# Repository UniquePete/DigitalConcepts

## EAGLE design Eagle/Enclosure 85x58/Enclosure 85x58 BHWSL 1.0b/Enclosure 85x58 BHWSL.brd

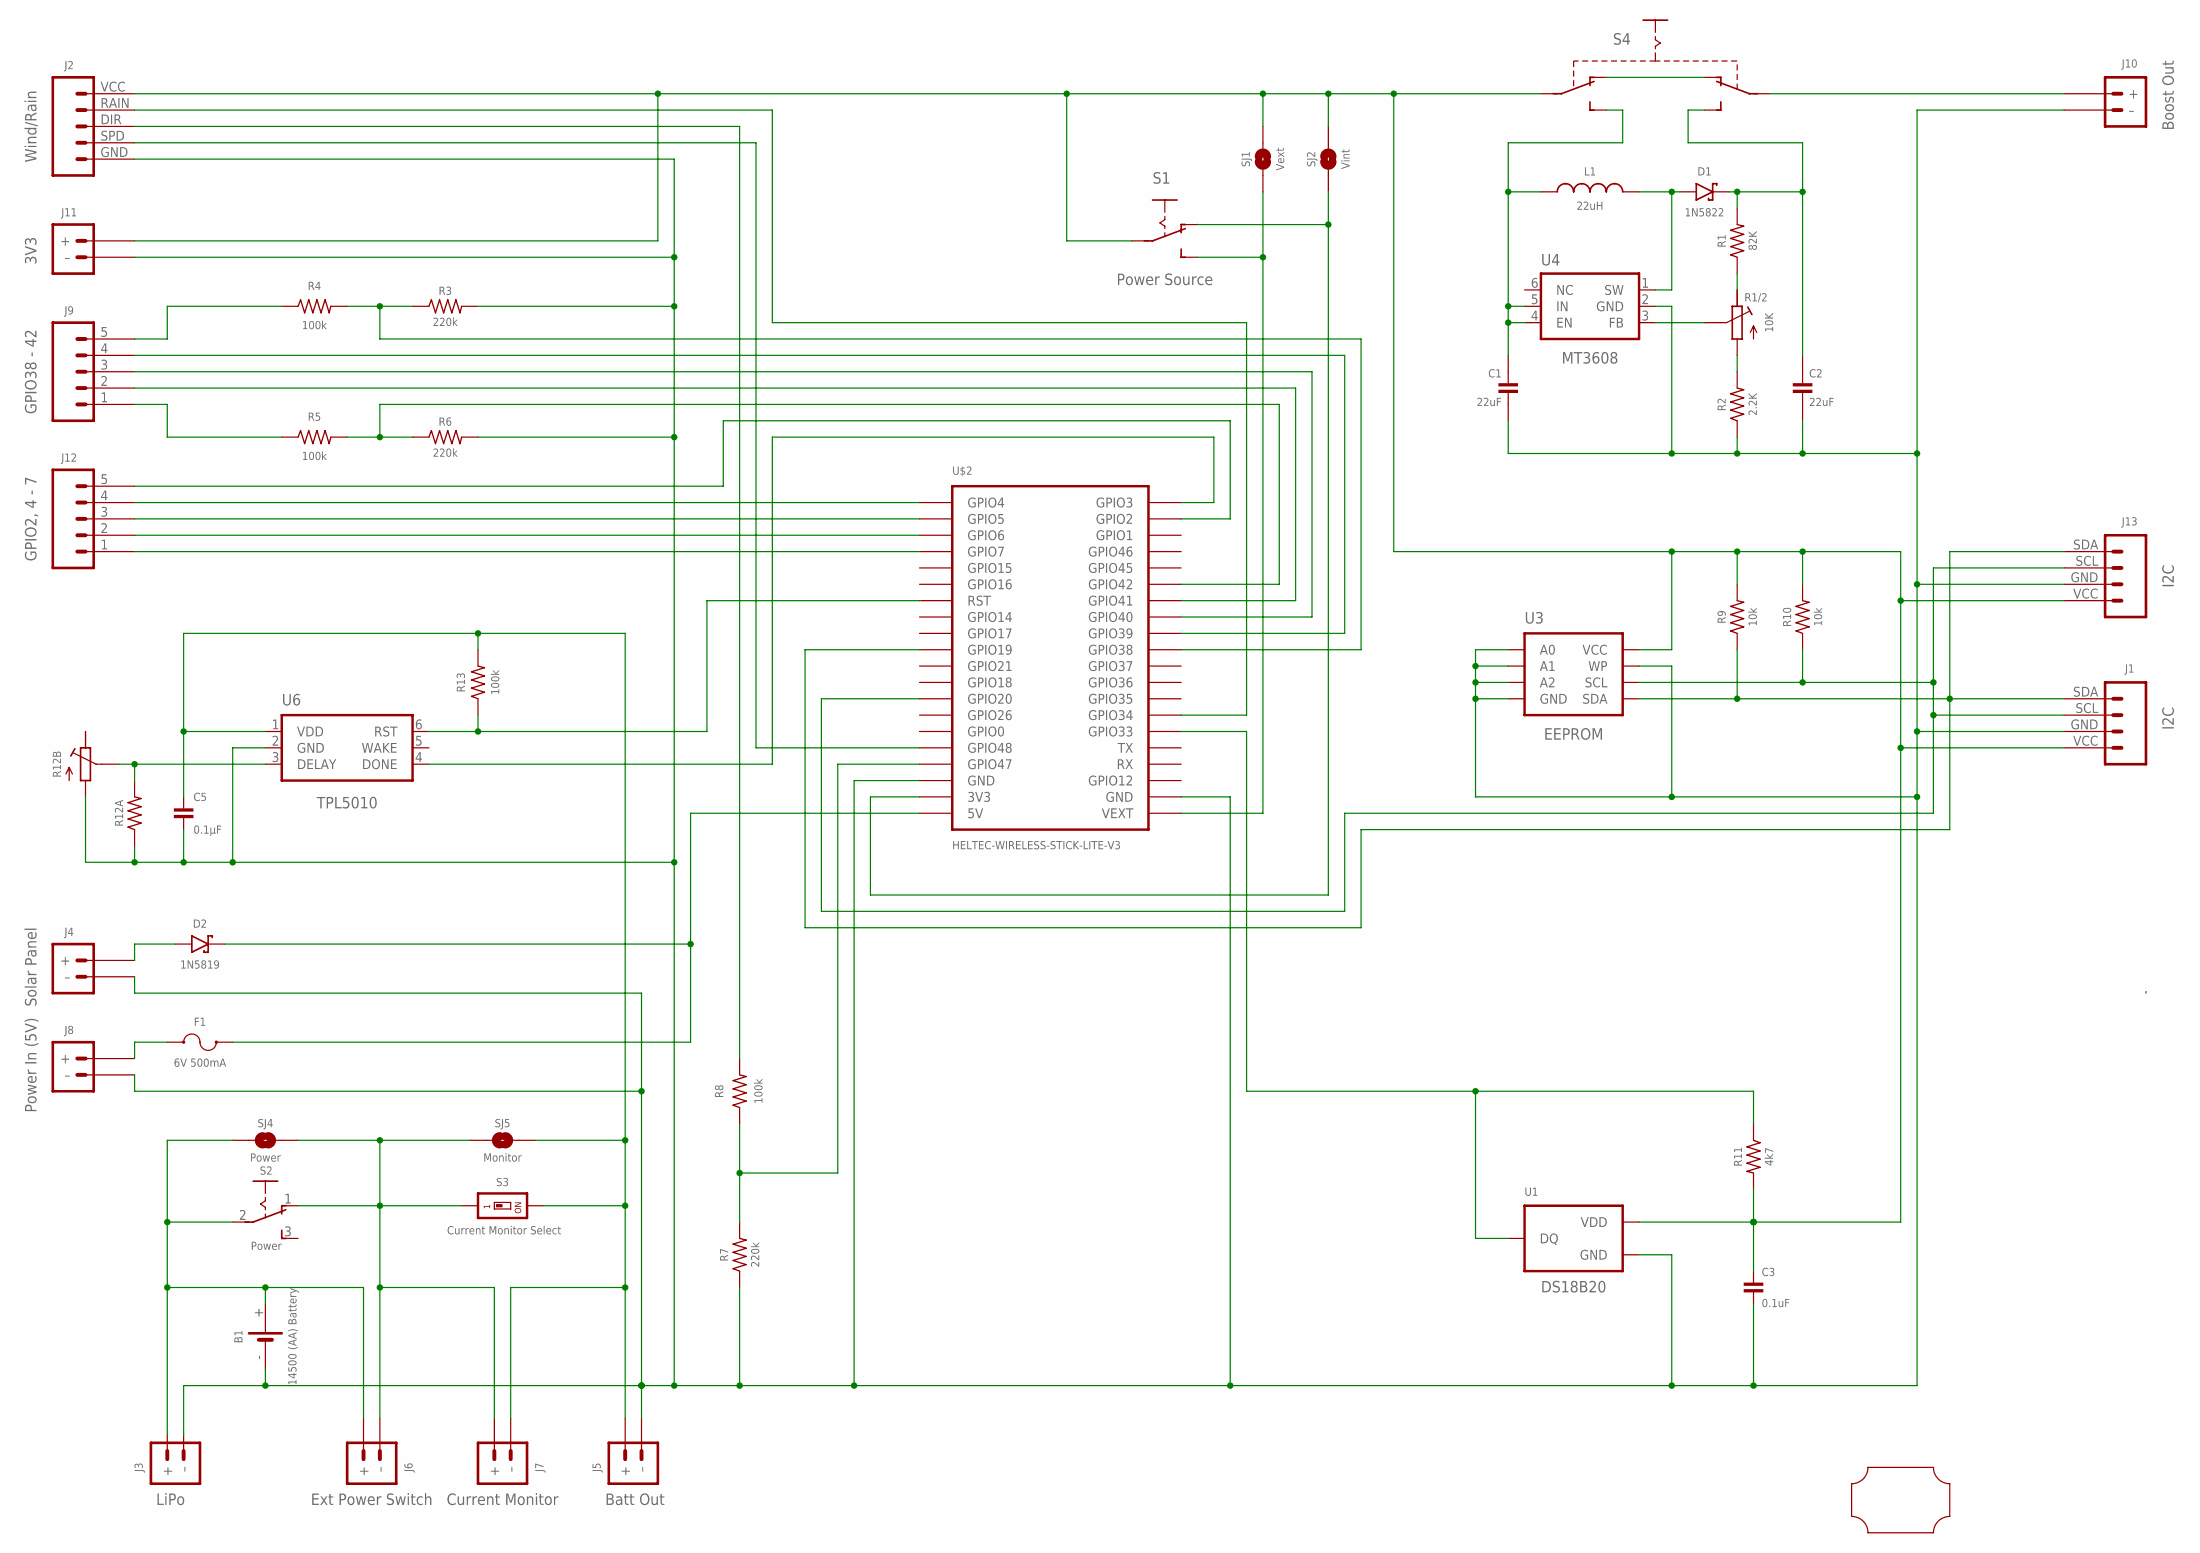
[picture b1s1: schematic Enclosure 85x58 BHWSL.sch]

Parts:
B1: 14500 (AA) Battery; BATTERY-14500
C1, C2: 22uF; C1206
C3: 0.1uF; C0805
C5: 0.1µF; C0805
D1: 1N5822; DIODE_SMB
D2: 1N5819; SOD-123
F1: 6V 500mA; F0805
J1: I2C; JST-PH2.0-4-VERTICAL-I2C
J2: Wind/Rain; JST-PH2.0-5-WEATHER
J3: LiPo; JST-PH2.0-2-HORIZONTAL
J4: Solar Panel; JST-PH2.0-2-VERTICAL-POWER
J5: Batt Out; JST-GH1.25-2-HORIZONTAL
J6: Ext Power Switch; JST-PH2.0-2-DUAL-POWER
J7: Current Monitor; JST-PH2.0-2-HORIZONTAL-POWER@1
J8: Power In (5V); JST-PH2.0-2-HORIZONTAL-POWER
J9: GPIO38 - 42; JST-PH2.0-5-HORIZONTAL
J10: Boost Out; JST-PH2.0-2-HORIZONTAL-POWER
J11: 3V3; JST-PH2.0-2-HORIZONTAL-POWER
J12: GPIO2, 4 - 7; JST-PH2.0-5-HORIZONTAL
J13: I2C; JST-PH2.0-4-HORIZONTAL-I2C
L1: 22uH; CDRH104R+6D28
R1: 82K; R0805
R1/2: 10K; RTRIM64P
R2: 2.2K; R0805
R3, R6, R7: 220k; R0805
R4, R5, R8, R13: 100k; R0805
R9, R10: 10k; R0805
R11: 4k7; R0805
R12A: RESISTORR0805; R0805
R12B: RESISTOR-TRIMM-33; RTRIM3*3
S1: Power Source; SWITCH-SPDT-SMT
S2: Power; SWITCH-SLIDE-SPDT
S3: Current Monitor Select; SMD-001
S4: SWITCH-SLIDE-DPDT-PTH-S; SWITCH-DPDT-PTH
SJ1: Vext; SJ
SJ2: Vint; SJ-VIA-1
SJ4: Power; SJ
SJ5: Monitor; SJ
U1: DS18B20; TO-92
U3: EEPROM; SOP-8
U4: MT3608; SOT-23-6@1
U6: TPL5010; SOT-23-6
U$1: PCB-OUTLINE-85X58; PROTO-28X18-OUTLINE
U$2: HELTEC-WIRELESS-STICK-LITE-V3

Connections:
GND: B1.-, C1.2, C2.2, C3.2, C5.2, J1.GND (3), J2.GND (5), J3.- (–), J4.- (–), J5.- (–), J8.- (–), J10.- (–), J11.- (–), J13.GND (3), R2.1, R3.2, R6.2, R7.1, R12A.1, R12B.1 (A), U1.1 (GND), U3.P$1 (A0), U3.P$2 (A1), U3.P$3 (A2), U3.P$4 (GND), U3.P$7 (WP), U4.2 (GND), U6.2 (GND), U$2.GND@18 (GND), U$2.GND@22 (GND)
unnamed: D2.A, J4.+
unnamed: J2.DIR (3), R8.2
unnamed: R1.1, R1/2.3 (E)
unnamed: B1.+, J3.+, J6.+, S2.2, SJ4.2
unnamed: D2.C, F1.2, U$2.5V
unnamed: D1.A, L1.1, U4.1 (SW)
unnamed: R7.2, R8.1, U$2.GPIO47
unnamed: J1.SCL (2), J13.SCL (2), R10.1, U3.P$6 (SCL), U$2.GPIO20
unnamed: J9.1, R5.1
unnamed: J12.5, U$2.GPIO2
unnamed: J1.SDA (1), J13.SDA (1), R9.1, U3.P$5 (SDA), U$2.GPIO19
unnamed: J2.SPD (4), U$2.GPIO48
unnamed: S1.P$1 (O), SJ2.2, U$2.3V3
unnamed: C5.1, J5.+, J7.- (–), R13.2, S3.2, SJ5.1, U6.1 (VDD)
unnamed: J12.4, U$2.GPIO4
unnamed: J12.3, U$2.GPIO5
unnamed: R11.1, U1.2 (DQ), U$2.GPIO33
unnamed: J12.2, U$2.GPIO6
unnamed: C2.1, D1.C, R1.2, S4.P$3 (S1)
unnamed: S1.P$2 (S), SJ1.2, U$2.VEXT
unnamed: J2.RAIN (2), U$2.GPIO34
unnamed: R1/2.1 (A), R2.2
unnamed: R1/2.2 (S), U4.3 (FB)
unnamed: C1.1, L1.2, S4.P$6 (S2), U4.4 (EN), U4.5 (IN)
unnamed: S4.P$1 (O1), S4.P$4 (O2)
unnamed: J10.+, S4.P$2 (P1)
unnamed: J12.1, U$2.GPIO7
unnamed: J9.2, U$2.GPIO41
unnamed: J9.3, U$2.GPIO40
unnamed: J9.4, U$2.GPIO39
unnamed: J9.5, R4.1
unnamed: R3.1, R4.2, U$2.GPIO38
unnamed: R5.2, R6.1, U$2.GPIO42
unnamed: R12A.2, R12B.2 (S), U6.3 (DELAY)
unnamed: R13.1, U6.6 (RST), U$2.RST
unnamed: U6.4 (DONE), U$2.GPIO3
unnamed: J6.- (–), J7.+, S2.1 (O), S3.1, SJ4.1, SJ5.2
unnamed: F1.1, J8.+
VCC: C3.1, J1.VCC (4), J2.VCC (1), J11.+, J13.VCC (4), R9.2, R10.2, R11.2, S1.COMMON, S4.P$5 (P2), SJ1.1, SJ2.1, SJ2.1@V (1), U1.3 (VDD), U3.P$8 (VCC)

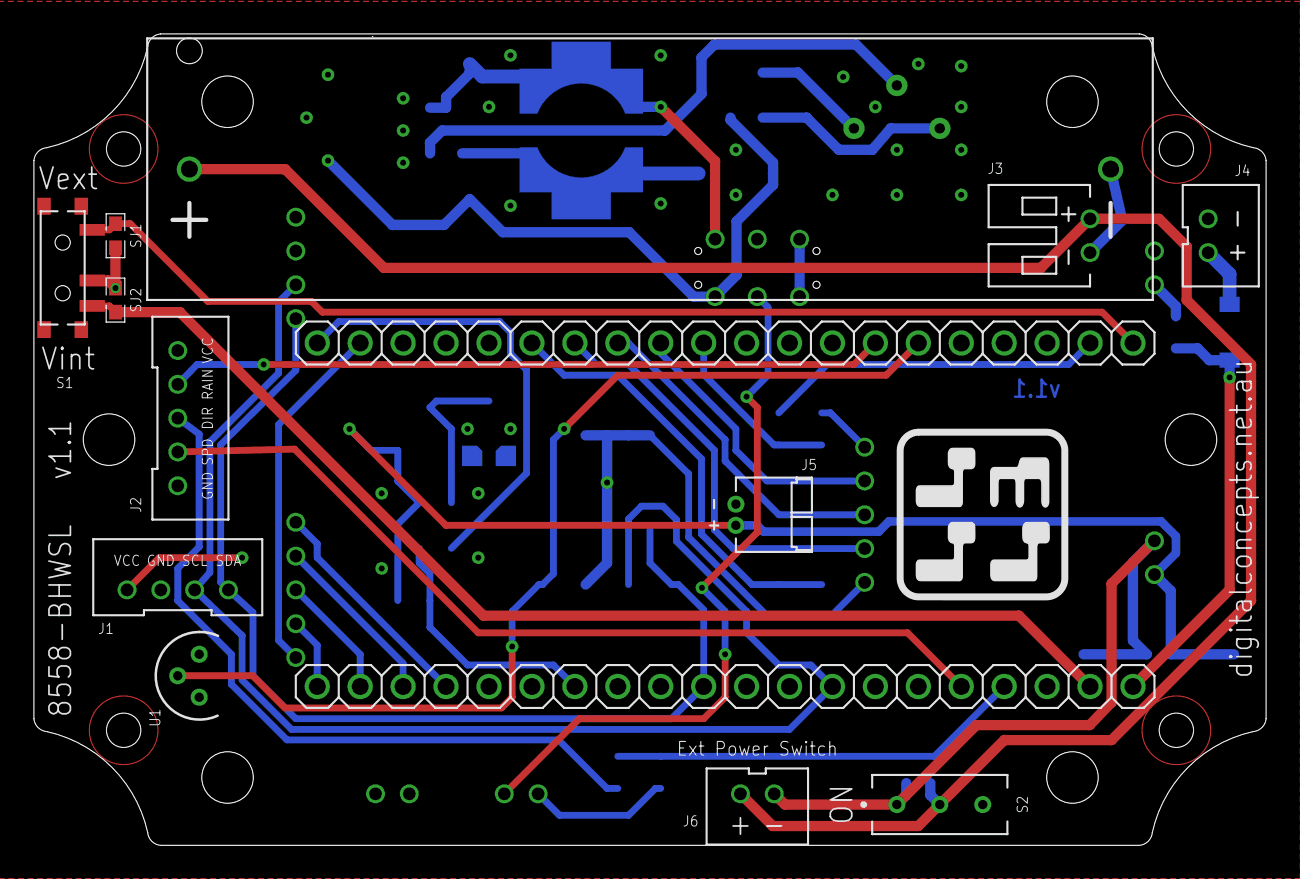
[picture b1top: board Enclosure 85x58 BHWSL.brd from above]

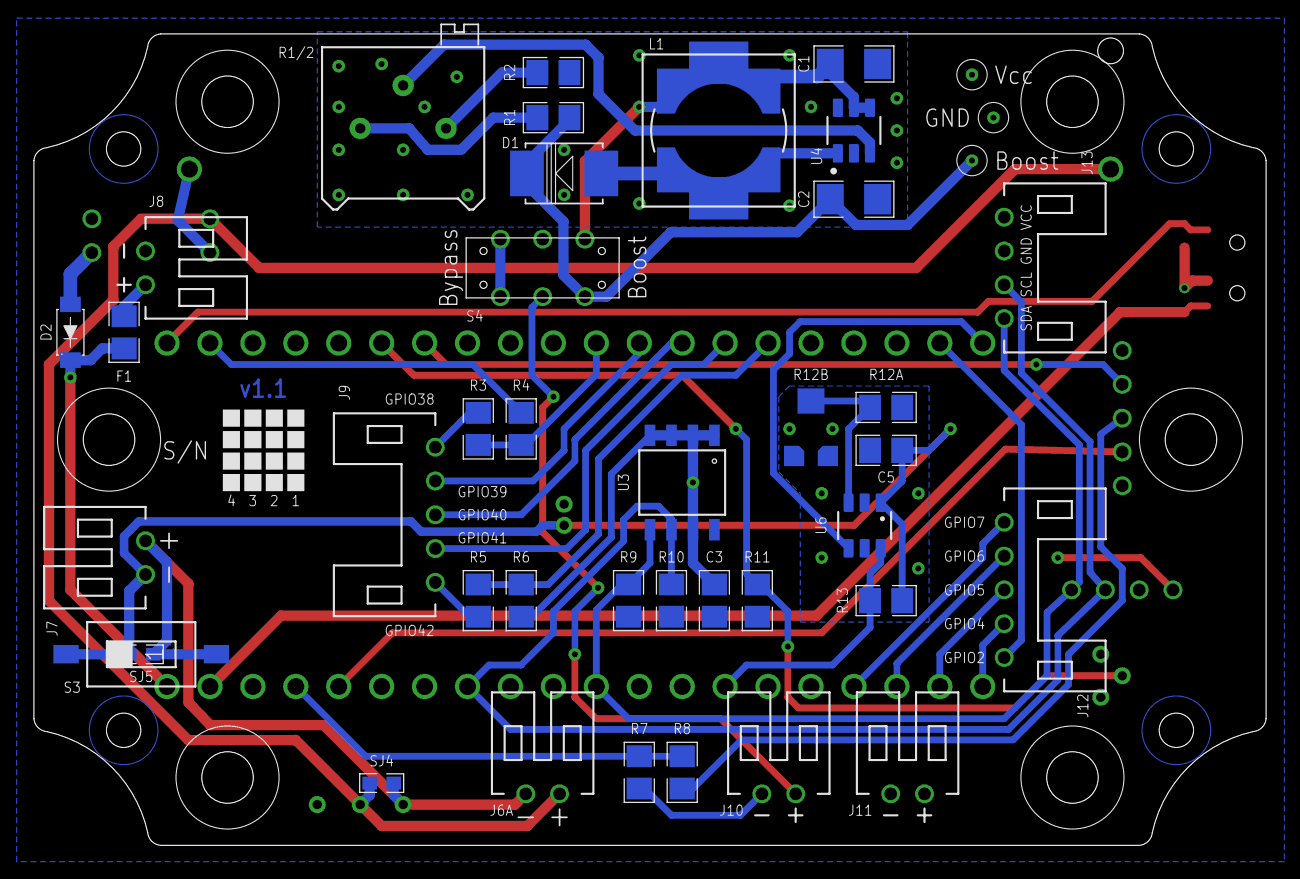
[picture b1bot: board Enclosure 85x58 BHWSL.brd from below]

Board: 2 copper layers, 72.9 x 48.0 mm, 51 parts (38 on the bottom side), 40 nets.
